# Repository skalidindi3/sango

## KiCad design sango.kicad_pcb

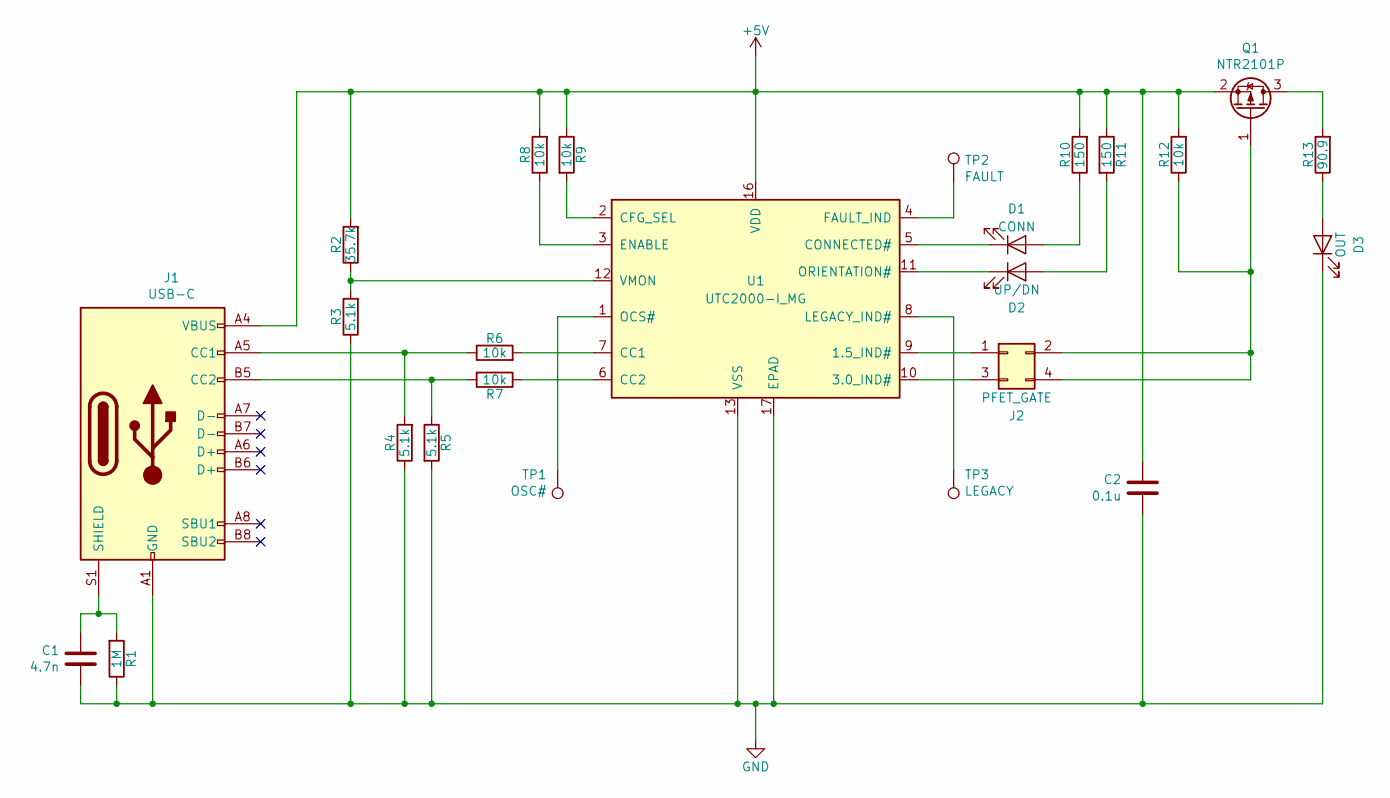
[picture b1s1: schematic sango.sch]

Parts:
C1: 4.7n; C_0805_2012Metric_Pad1.15x1.40mm_HandSolder; Manufacturer Part Number CL21C4R7BBANNNC
C2: 0.1u; C_0805_2012Metric_Pad1.15x1.40mm_HandSolder; Manufacturer Part Number CL21B104MBCNNNC
D1: CONN; LED_0805_2012Metric_Pad1.15x1.40mm_HandSolder; Manufacturer Part Number 150080RS75000
D2: UP/DN; LED_0805_2012Metric_Pad1.15x1.40mm_HandSolder; Manufacturer Part Number 150080YS75000
D3: OUT; LED_0805_2012Metric_Pad1.15x1.40mm_HandSolder; Manufacturer Part Number 150080BS75000
J1: USB-C; USB_C_Receptacle_Amphenol_12401598E4-2A; Manufacturer Part Number 12401598E4#2A
J2: PFET_GATE; PinHeader_2x02_P2.54mm_Vertical; Manufacturer Part Number PRPC002DAAN-RC
Q1: NTR2101P; SOT-23; Manufacturer Part Number NTR2101PT1G
R1: 1M; R_0805_2012Metric_Pad1.15x1.40mm_HandSolder; Manufacturer Part Number ERJ-6ENF1004V
R2: 35.7k; R_0805_2012Metric_Pad1.15x1.40mm_HandSolder; Manufacturer Part Number ERJ-6ENF3572V
R3, R4, R5: 5.1k; R_0805_2012Metric_Pad1.15x1.40mm_HandSolder; Manufacturer Part Number ERJ-6ENF5101V
R6, R7, R8, R9, R12: 10k; R_0805_2012Metric_Pad1.15x1.40mm_HandSolder; Manufacturer Part Number ERJ-6ENF1002V
R10, R11: 150; R_0805_2012Metric_Pad1.15x1.40mm_HandSolder; Manufacturer Part Number ERJ-6ENF1500V
R13: 90.9; R_0805_2012Metric_Pad1.15x1.40mm_HandSolder; Manufacturer Part Number ERJ-6ENF90R9V
TP1: OSC#; TestPoint_Pad_D2.0mm
TP2: FAULT; TestPoint_Pad_D2.0mm
TP3: LEGACY; TestPoint_Pad_D2.0mm
U1: UTC2000-I_MG; UTC2000; Manufacturer Part Number UTC2000-I/MG

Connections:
+5V: C2.2, J1.A4 (VBUS), J1.A9 (VBUS), J1.B4 (VBUS), J1.B9 (VBUS), Q1.2 (S), R2.2, R8.2, R9.1, R10.2, R11.1, R12.2, U1.16 (VDD)
GND: C1.1, C2.1, D3.1 (K), J1.A1 (GND), J1.A12 (GND), J1.B1 (GND), J1.B12 (GND), R1.1, R3.1, R4.1, R5.2, U1.13 (VSS), U1.17 (EPAD)
unnamed: C1.2, J1.S1 (SHIELD), R1.2
unnamed: D1.1 (K), U1.5 (CONNECTED#)
unnamed: D1.2 (A), R10.1
unnamed: D2.1 (K), U1.11 (ORIENTATION#)
unnamed: D2.2 (A), R11.2
unnamed: D3.2 (A), R13.1
unnamed: J1.A5 (CC1), R4.2, R6.1
unnamed: J1.B5 (CC2), R5.1, R7.2
unnamed: J2.1, U1.9 (1.5_IND#)
unnamed: J2.2, J2.4, Q1.1 (G), R12.1
unnamed: J2.3, U1.10 (3.0_IND#)
unnamed: Q1.3 (D), R13.2
unnamed: R2.1, R3.2, U1.12 (VMON)
unnamed: R6.2, U1.7 (CC1)
unnamed: R7.1, U1.6 (CC2)
unnamed: R8.1, U1.3 (ENABLE)
unnamed: R9.2, U1.2 (CFG_SEL)
unnamed: TP1.1, U1.1 (OCS#)
unnamed: TP2.1, U1.4 (FAULT_IND)
unnamed: TP3.1, U1.8 (LEGACY_IND#)

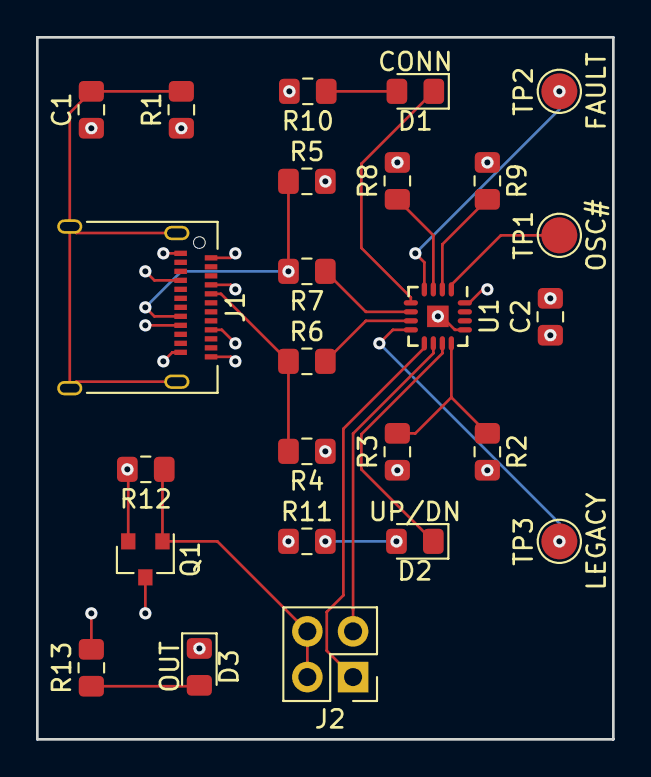
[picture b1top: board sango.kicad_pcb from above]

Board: 4 copper layers, 32.0 x 39.0 mm, 25 parts (0 on the bottom side), 22 nets.

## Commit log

2018-01-03 init commit: init project
2018-01-09 add UTC2000 to microchip symbols lib
2018-11-09 Kicad 5 compatibility upgrade
    - replace USB Type-C receptacle with Kicad 5 version
    - decoupling RC from shield to GND
    - added .gitignore
2018-11-12 add high-side driver pFET
2018-11-12 fix: OSC --> OCS typo
2018-11-18 add Description field to UTC2000 schematic symbol
2018-11-18 fix: resistor value for voltage divider on VMON
2018-11-18 add part numbers for resistors and PFET
2018-11-18 add LEDs and testpads, re-center
2018-11-18 add ilim R for output LED
    - part numbers for remaining resistors
    - rename LEDs for associated color
2018-11-19 switch resistors from 0603 --> 0805
2018-11-19 add footprints for 0805 resistors
2018-11-19 add UTC2000 footprint
2018-11-20 add usb type-c receptable symbol modification to stdlibmods lib
2018-11-20 add conn 02x02 symbol modification to stdlibmods lib
2018-11-20 add jumpers for wired-or pfet gate operation
2018-11-20 add decoupling 0.1uF for UTC2000, fill out fields for caps
2018-11-20 assign footprint for UTC2000
2018-11-20 assign 2mm diameter pad footprint to testpads
2018-11-20 add Amphenol 12401598E4-2A usbc receptable footprint & 3d model
2018-11-20 assign usbc receptable footprint & set fields
2018-11-20 assign jumper pin header footprint & set fields
2018-11-20 assign LED footprints & set fields
2018-11-20 annotate schematic
2018-11-20 generate netlist
2018-11-20 initial layout
    - add kicad_pcb-bak to gitignore
    - switch LED names for adding to silkscreen
2018-11-21 added rules for 4-layer OSHpark fab
2018-11-21 init 4-layer layout
    - TODO: expand trace thickness past minimum
    - TODO: review whether placing vias on pads is ok
    - TODO: add silkscreen indicating which jumper is which
    - TODO: board graphics
2019-03-12 add LT1930A to linear technology symbols lib
2019-03-12 separate current schematic into 'USB-C Power' sheet
2019-03-12 rework usb-c power according to Mike's review
    - some symbol changes for UTC2000, USB-C receptacle
    - remove LED for orientation
    - add LED for fault
    - extend pin header for legacy_ind, orientation, & gnd
    - remove test point for OCS#
    - add TODOs as text
2019-03-12 add 'DCDC Bipolar Supply' sheet w/ init schematic
2019-03-12 fix direction of 5V_OUT sheet label
2019-03-12 clone LT1930A part for LT1930
2019-03-12 swap LT1930A for LT1930 in DCDC bipolar supply
2019-03-12 remove default footprint for LT1930x
2019-04-04 add LT3045 & LT3094 symbols
2019-04-04 add sheets for +/-12V LDOs
2019-04-04 add schematics for LDO sheets
2019-04-10 update schematic after LTSpice simulations
    - enable EN/UV and PGFB usage for LDOs
    - PGFB required for fast startup
    - EN/UV required to allow boost to ramp up
    - take care of some TODOs in usbc-power sch
2019-04-11 remove false desc for copied resistors in ldo schematics
2019-04-11 add BOM info for schottky diodes & LT1930
2019-04-11 update hierarchal pin names to be accurate to new settings
2019-04-11 update resistor BOM for ldo sheets
2019-04-12 replace LDO SET resistors with high-precision thin (metal) film variants
2019-04-12 comments in negative LDO sheet
2019-04-12 BOM details for DC/DC FB resistors
2019-04-12 BOM details for LDOs
2019-04-12 remove BOM details of copied caps
2019-04-12 add footprint for schottky diodes
2019-04-14 replace USB Type-C connector
2019-04-14 add .DS_Store to .gitignore
2019-04-14 add 6.35mm jack footprint & model
2019-04-16 add init audio.sch sheet
2019-05-28 add init NJR symbols lib with NJM2068
2019-05-28 flesh out audio amp sheet, without R/C values
2019-06-10 add ipython notebook with notes & LTspice sim plots
2019-06-10 add audio amp gain stage values
2019-06-11 add audio amp output stage values
2019-06-12 finish usbc sch component selection
2019-06-12 finish dcdc sch component selection
2019-06-13 change LDO sch capacitors & finish component selection
2019-06-13 add components for caps in audio.sch
2019-06-13 add components for audo.sch
2019-06-14 fix field ordering in dcdc-bipolar-supply & usb-c-power
2019-06-14 update audio jack connections
2019-06-14 switch Z_out resistors to 2 ohms & select components
2019-06-14 add ic sockets for the 3 op amps
2019-06-14 add ic socket model
2019-06-14 use local socket & model
2019-06-14 add op amp components
2019-06-14 match audio jack to footprint
2019-06-14 add audio pot model
2019-06-14 switch to 4.7uF WIMA caps in output stage
2019-06-14 add missing NJM2068 BOM data
2019-06-18 swap output stage highpass resistors to 40.2k
2019-06-19 update dcdc feedback config & components
2019-06-19 switch components supplier to Mouser for price/availability
2019-06-19 update ldo threshold configs & components
2019-06-21 add audio pot components & model
2019-06-21 add pushbutton model, footprint, & components
2019-06-21 fix audio pot label & other label sizing
2019-06-22 add circuit notes
2019-06-22 center placement of circuits in schematic sheets
2019-06-22 cleanup of wiring & notes in audio.sch
2019-06-22 update usb indicators breakout
2019-06-25 swap usbc connector model
2019-06-25 fix MSOP12 default lib model path
2019-06-29 add bourns SRU5028A inductor model & footprint
    - switch location of bourns pot footprint
    - update sourcing
2019-06-29 switch inductor to bourns SRU5028A
2019-06-29 remove old netlist and layout
2019-09-01 add output stage ipython notebook calculations
2019-09-01 replace bourns audio pot for alps (target jade version)
2019-09-01 update output high pass filter
    - replace WIMA 4.7uF coupling caps for KEMET 1uF
    - replace 40.2k resistors with 274k
    - update note
2019-09-01 update output stage coupled caps
